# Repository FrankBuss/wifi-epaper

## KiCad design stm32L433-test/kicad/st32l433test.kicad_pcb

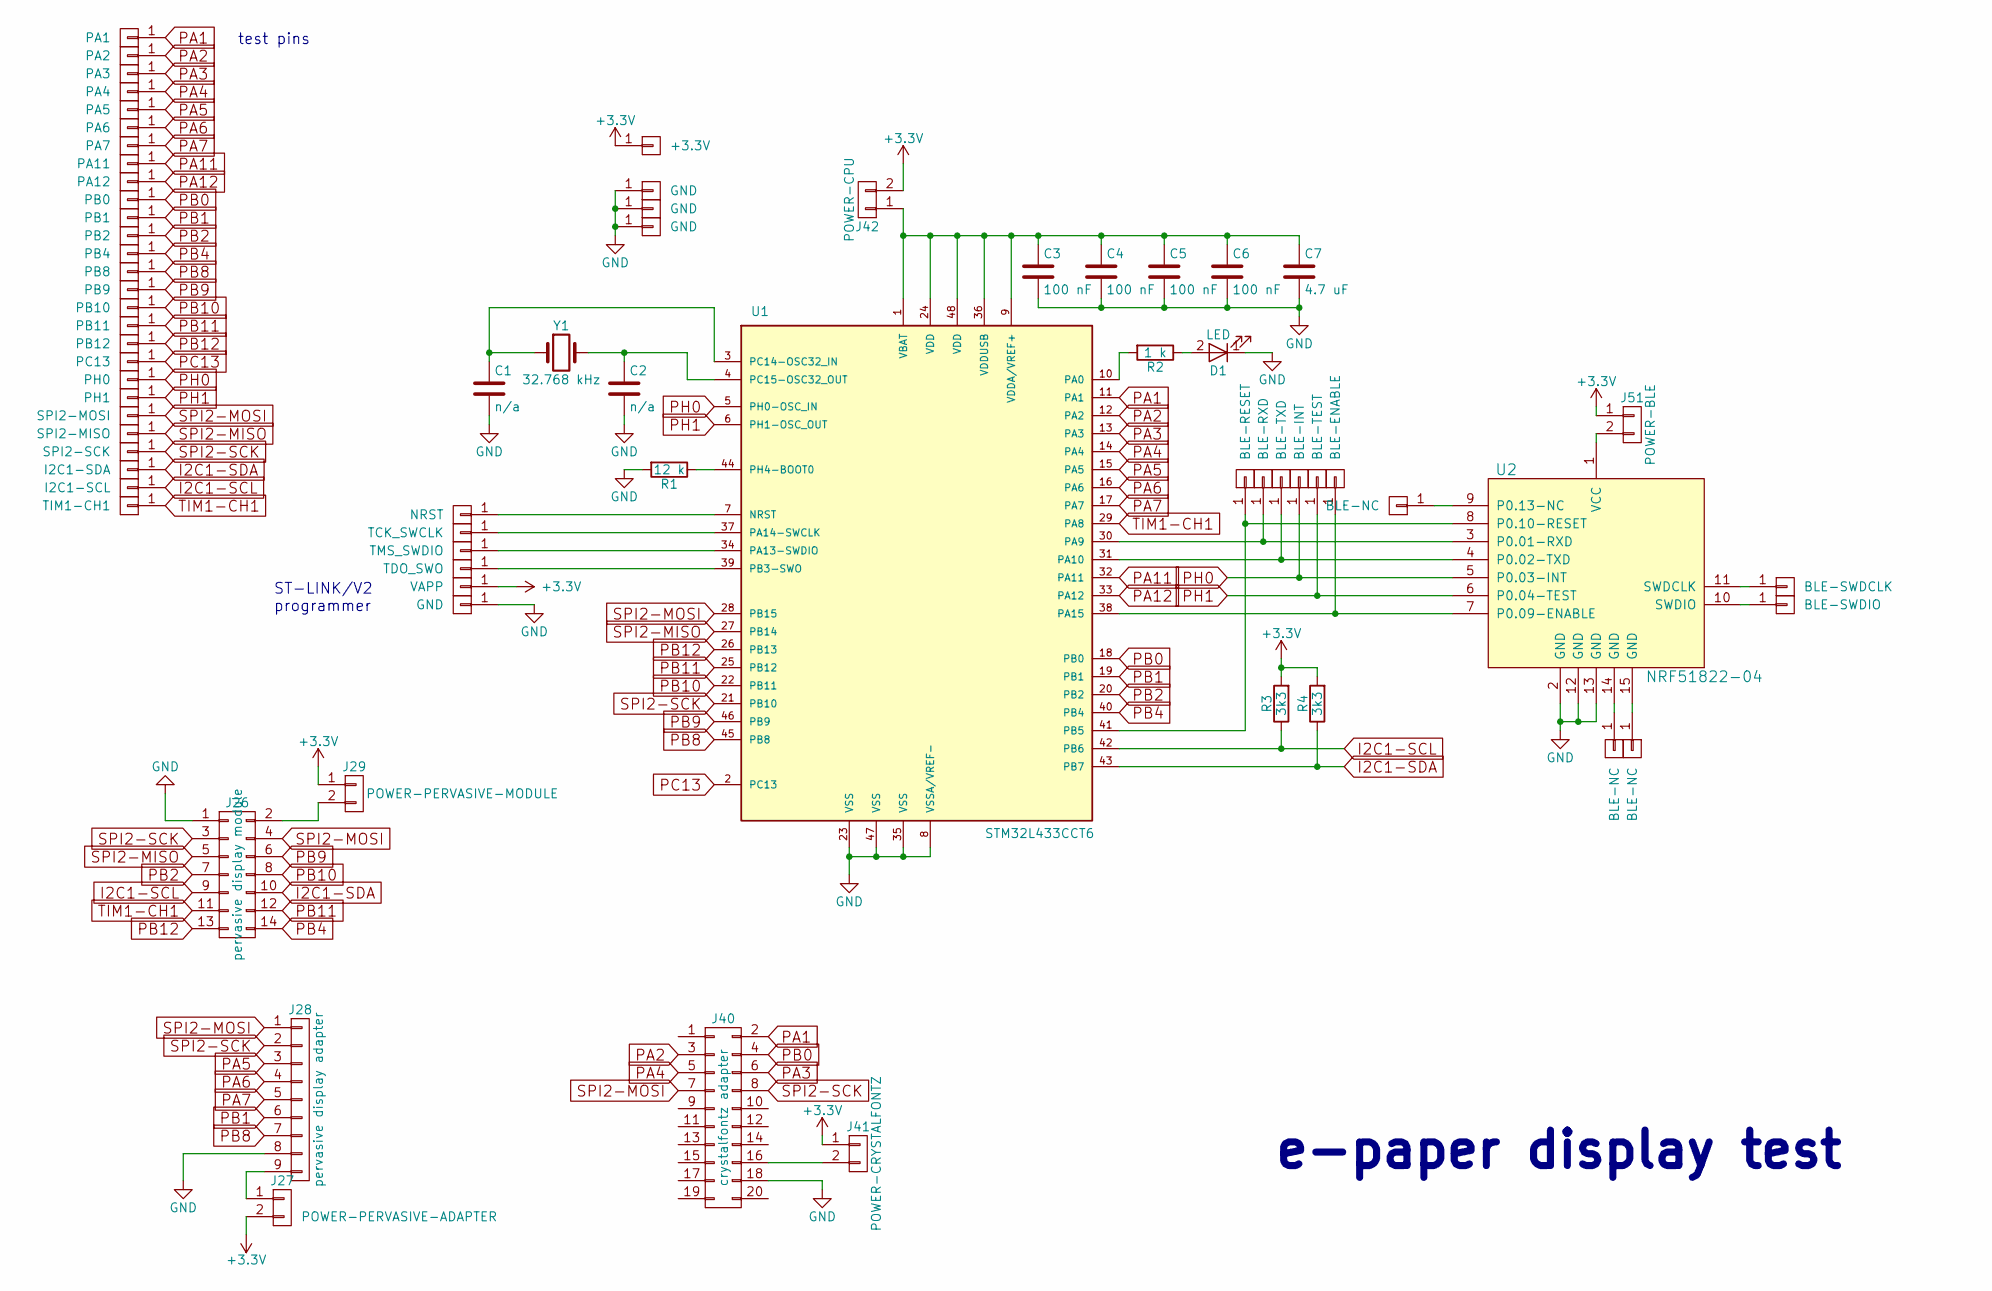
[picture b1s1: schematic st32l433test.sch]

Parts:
C1, C2: n/a; C_0805_HandSoldering
C3, C4, C5, C6: 100 nF; C_0805_HandSoldering
C7: 4.7 uF; C_0805_HandSoldering
D1: LED; LED_D3.0mm
J1: PA1; Pin_Header_Straight_1x01_Pitch2.54mm
J2: PA2; Pin_Header_Straight_1x01_Pitch2.54mm
J3: PA3; Pin_Header_Straight_1x01_Pitch2.54mm
J4: PA4; Pin_Header_Straight_1x01_Pitch2.54mm
J5: PA5; Pin_Header_Straight_1x01_Pitch2.54mm
J6: PA6; Pin_Header_Straight_1x01_Pitch2.54mm
J7: PA7; Pin_Header_Straight_1x01_Pitch2.54mm
J8: PB0; Pin_Header_Straight_1x01_Pitch2.54mm
J9: PB1; Pin_Header_Straight_1x01_Pitch2.54mm
J10: PB2; Pin_Header_Straight_1x01_Pitch2.54mm
J11: PB4; Pin_Header_Straight_1x01_Pitch2.54mm
J12: PB8; Pin_Header_Straight_1x01_Pitch2.54mm
J13: PB9; Pin_Header_Straight_1x01_Pitch2.54mm
J14: PB10; Pin_Header_Straight_1x01_Pitch2.54mm
J15: PB11; Pin_Header_Straight_1x01_Pitch2.54mm
J16: PB12; Pin_Header_Straight_1x01_Pitch2.54mm
J17: PC13; Pin_Header_Straight_1x01_Pitch2.54mm
J18: PH0; Pin_Header_Straight_1x01_Pitch2.54mm
J19: PH1; Pin_Header_Straight_1x01_Pitch2.54mm
J20: SPI2-MOSI; Pin_Header_Straight_1x01_Pitch2.54mm
J21: SPI2-MISO; Pin_Header_Straight_1x01_Pitch2.54mm
J22: SPI2-SCK; Pin_Header_Straight_1x01_Pitch2.54mm
J23: I2C1-SDA; Pin_Header_Straight_1x01_Pitch2.54mm
J24: I2C1-SCL; Pin_Header_Straight_1x01_Pitch2.54mm
J25: TIM1-CH1; Pin_Header_Straight_1x01_Pitch2.54mm
J26: pervasive display module; Pin_Header_Straight_2x07_Pitch2.54mm
J27: POWER-PERVASIVE-ADAPTER; Pin_Header_Straight_1x02_Pitch2.54mm
J28: pervasive display adapter; Pin_Header_Straight_1x09_Pitch2.54mm
J29: POWER-PERVASIVE-MODULE; Pin_Header_Straight_1x02_Pitch2.54mm
J30: NRST; Pin_Header_Straight_1x01_Pitch2.54mm
J31: TCK_SWCLK; Pin_Header_Straight_1x01_Pitch2.54mm
J32: TMS_SWDIO; Pin_Header_Straight_1x01_Pitch2.54mm
J33: TDO_SWO; Pin_Header_Straight_1x01_Pitch2.54mm
J34: VAPP; Pin_Header_Straight_1x01_Pitch2.54mm
J35, J37, J38, J39: GND; Pin_Header_Straight_1x01_Pitch2.54mm
J36: +3.3V; Pin_Header_Straight_1x01_Pitch2.54mm
J40: crystalfontz adapter; Pin_Header_Straight_2x10_Pitch2.54mm
J41: POWER-CRYSTALFONTZ; Pin_Header_Straight_1x02_Pitch2.54mm
J42: POWER-CPU; Pin_Header_Straight_1x02_Pitch2.54mm
J43: BLE-RESET; Pin_Header_Straight_1x01_Pitch2.54mm
J44: BLE-RXD; Pin_Header_Straight_1x01_Pitch2.54mm
J45: BLE-TXD; Pin_Header_Straight_1x01_Pitch2.54mm
J46: BLE-INT; Pin_Header_Straight_1x01_Pitch2.54mm
J47: BLE-TEST; Pin_Header_Straight_1x01_Pitch2.54mm
J48: BLE-ENABLE; Pin_Header_Straight_1x01_Pitch2.54mm
J49, J50, J52: BLE-NC; Pin_Header_Straight_1x01_Pitch2.54mm
J51: POWER-BLE; Pin_Header_Straight_1x02_Pitch2.54mm
J53: BLE-SWDCLK; Pin_Header_Straight_1x01_Pitch2.54mm
J54: BLE-SWDIO; Pin_Header_Straight_1x01_Pitch2.54mm
J55: PA11; Pin_Header_Straight_1x01_Pitch2.54mm
J56: PA12; Pin_Header_Straight_1x01_Pitch2.54mm
R1: 12 k; R_0805_HandSoldering
R2: 1 k; R_0805_HandSoldering
R3, R4: 3k3; R_0805_HandSoldering
U1: STM32L433CCT6; LQFP-48_7x7mm_Pitch0.5mm
U2: NRF51822-04
Y1: 32.768 kHz; crystal

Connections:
+3V3: J27.2, J29.1, J34.1, J36.1, J41.1, J42.2, J51.1, R3.2, R4.2
GND: C1.2, C2.2, C3.2, C4.2, C5.2, C6.2, C7.2, D1.1 (K), J26.1, J28.8, J35.1, J37.1, J38.1, J39.1, J40.18, R1.2, U1.8 (VSSA/VREF-), U1.23 (VSS), U1.35 (VSS), U1.47 (VSS), U2.2 (GND), U2.12 (GND), U2.13 (GND)
I2C1-SCL: J24.1, J26.9, R3.1, U1.42 (PB6)
I2C1-SDA: J23.1, J26.10, R4.1, U1.43 (PB7)
unnamed: C1.1, U1.3 (PC14-OSC32_IN), Y1.1
unnamed: C2.1, U1.4 (PC15-OSC32_OUT), Y1.2
unnamed: C3.1, C4.1, C5.1, C6.1, C7.1, J42.1, U1.1 (VBAT), U1.9 (VDDA/VREF+), U1.24 (VDD), U1.36 (VDDUSB), U1.48 (VDD)
unnamed: D1.2 (A), R2.1
unnamed: J26.2, J29.2
unnamed: J27.1, J28.9
unnamed: J30.1, U1.7 (NRST)
unnamed: J31.1, U1.37 (PA14-SWCLK)
unnamed: J32.1, U1.34 (PA13-SWDIO)
unnamed: J33.1, U1.39 (PB3-SWO)
unnamed: J40.16, J41.2
unnamed: J43.1, U1.41 (PB5), U2.8 (P0.10-RESET)
unnamed: J44.1, U1.30 (PA9), U2.3 (P0.01-RXD)
unnamed: J45.1, U1.31 (PA10), U2.4 (P0.02-TXD)
unnamed: J48.1, U1.38 (PA15), U2.7 (P0.09-ENABLE)
unnamed: J49.1, U2.9 (P0.13-NC)
unnamed: J50.1, U2.14 (GND)
unnamed: J51.2, U2.1 (VCC)
unnamed: J52.1, U2.15 (GND)
unnamed: J53.1, U2.11 (SWDCLK)
unnamed: J54.1, U2.10 (SWDIO)
unnamed: R1.1, U1.44 (PH4-BOOT0)
unnamed: R2.2, U1.10 (PA0)
PA1: J1.1, J40.2, U1.11 (PA1)
PA2: J2.1, J40.3, U1.12 (PA2)
PA3: J3.1, J40.6, U1.13 (PA3)
PA4: J4.1, J40.5, U1.14 (PA4)
PA5: J5.1, J28.3, U1.15 (PA5)
PA6: J6.1, J28.4, U1.16 (PA6)
PA7: J7.1, J28.5, U1.17 (PA7)
PA11: J55.1, U1.32 (PA11)
PA12: J56.1, U1.33 (PA12)
PB0: J8.1, J40.4, U1.18 (PB0)
PB1: J9.1, J28.6, U1.19 (PB1)
PB2: J10.1, J26.7, U1.20 (PB2)
PB4: J11.1, J26.14, U1.40 (PB4)
PB8: J12.1, J28.7, U1.45 (PB8)
PB9: J13.1, J26.6, U1.46 (PB9)
PB10: J14.1, J26.8, U1.22 (PB11)
PB11: J15.1, J26.12, U1.25 (PB12)
PB12: J16.1, J26.13, U1.26 (PB13)
PC13: J17.1, U1.2 (PC13)
PH0: J18.1, J46.1, U1.5 (PH0-OSC_IN), U2.5 (P0.03-INT)
PH1: J19.1, J47.1, U1.6 (PH1-OSC_OUT), U2.6 (P0.04-TEST)
SPI2-MISO: J21.1, J26.5, U1.27 (PB14)
SPI2-MOSI: J20.1, J26.4, J28.1, J40.7, U1.28 (PB15)
SPI2-SCK: J22.1, J26.3, J28.2, J40.8, U1.21 (PB10)
TIM1-CH1: J25.1, J26.11, U1.29 (PA8)

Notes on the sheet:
ST-LINK/V2 programmer
test pins
e-paper display test

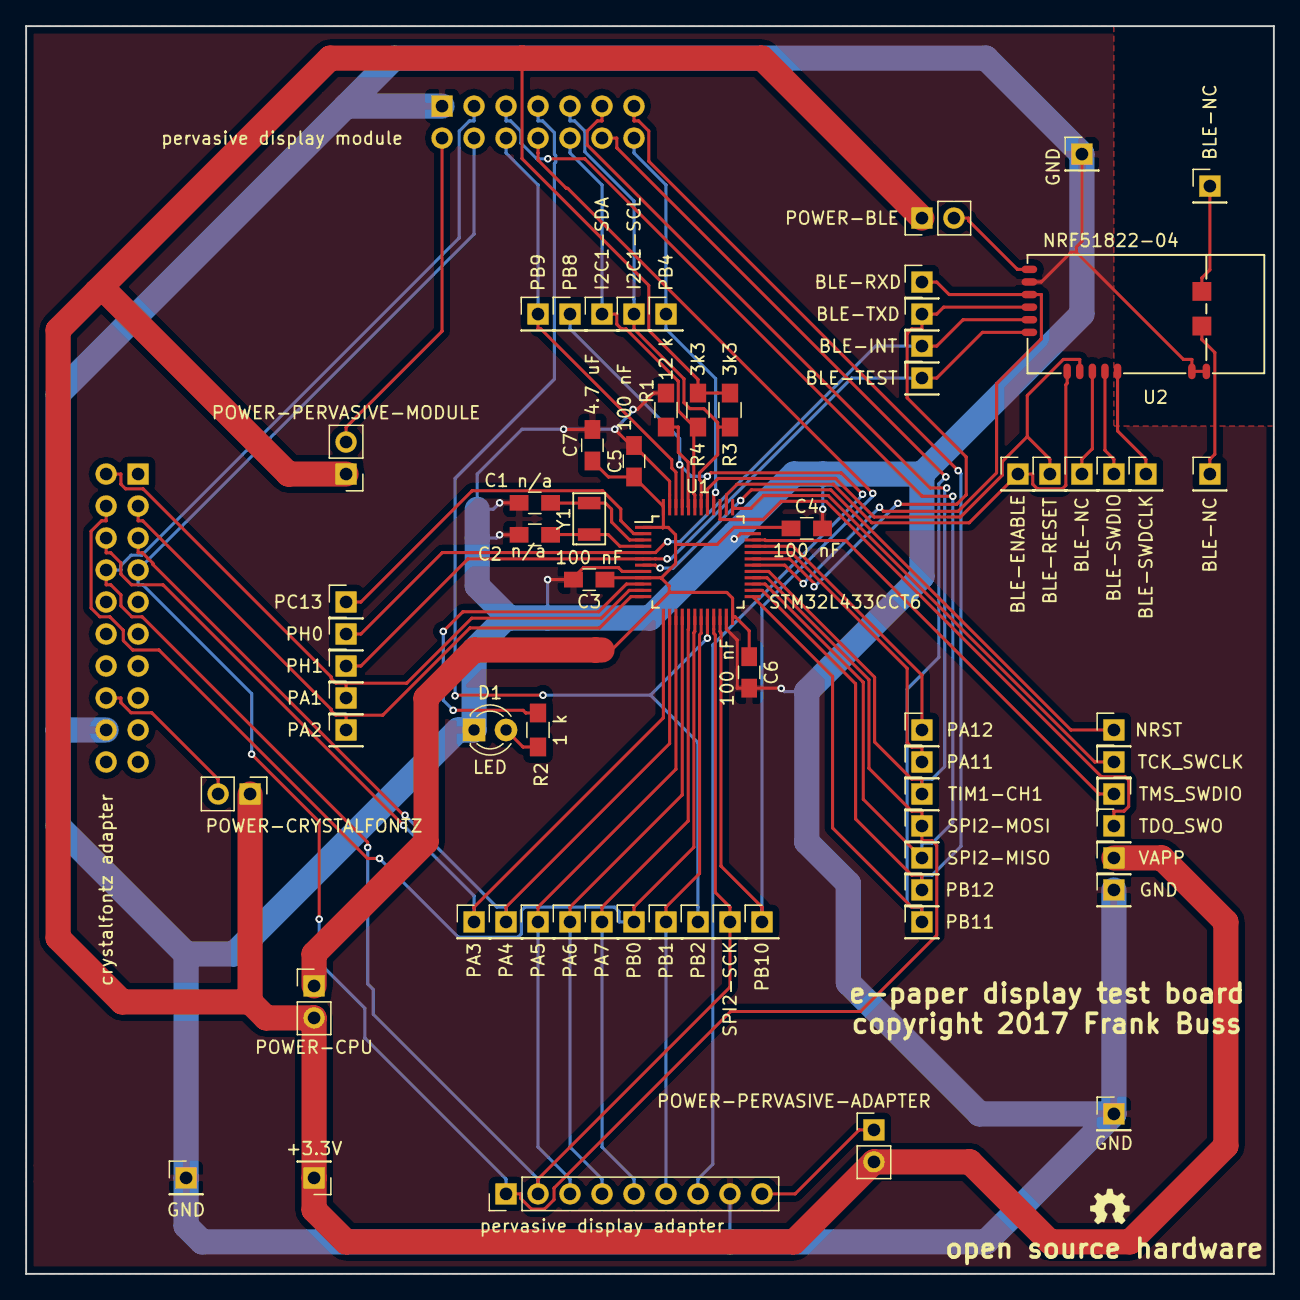
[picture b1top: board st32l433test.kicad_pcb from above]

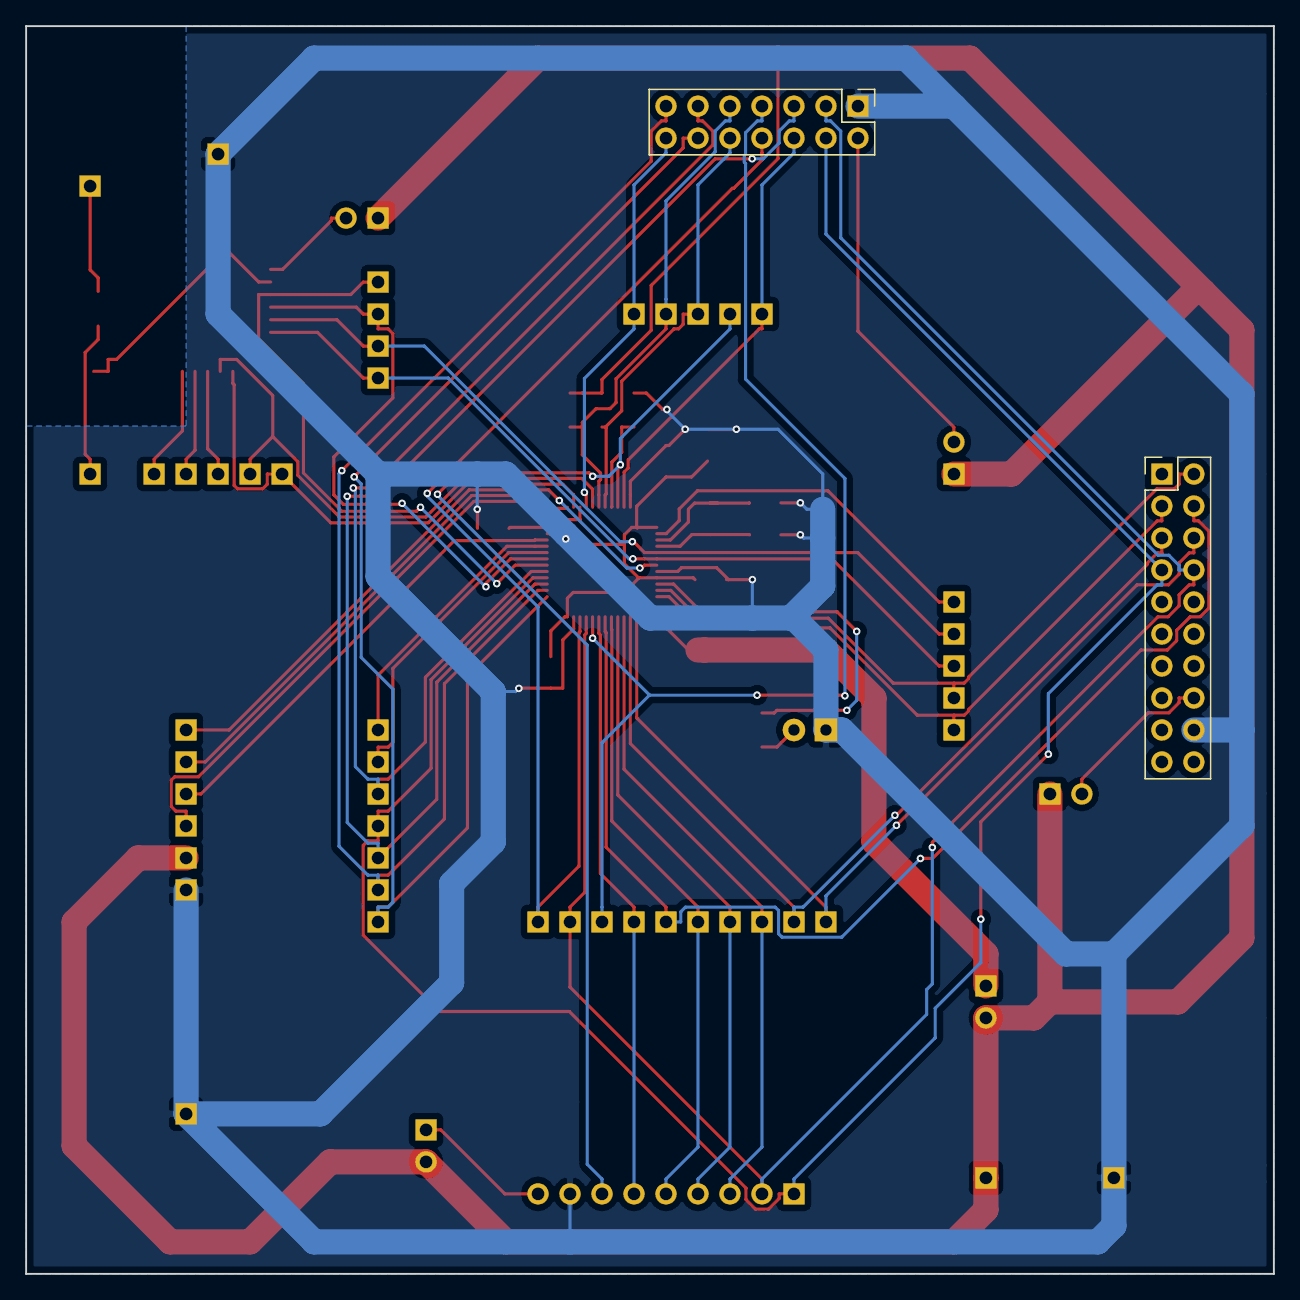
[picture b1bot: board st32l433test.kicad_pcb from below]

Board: 2 copper layers, 99.1 x 99.1 mm, 71 parts (2 on the bottom side), 52 nets.

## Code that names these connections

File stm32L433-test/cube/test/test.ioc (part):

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Mcu.Name=STM32L433C(B-C)Tx
Mcu.Package=LQFP48
Mcu.UserName=STM32L433CCTx
PA0.Signal=GPIO_Output
PA1.Signal=GPIO_Output
PA10.Mode=Asynchronous
PA10.Signal=USART1_RX
PA11.Mode=Device
PA11.Signal=USB_DM
PA12.Mode=Device
PA12.Signal=USB_DP
PA13\ (JTMS-SWDIO).Mode=Serial_Wire
PA13\ (JTMS-SWDIO).Signal=SYS_JTMS-SWDIO
PA14\ (JTCK-SWCLK).Mode=Serial_Wire
PA14\ (JTCK-SWCLK).Signal=SYS_JTCK-SWCLK
PA2.Signal=GPIO_Output
PA3.Signal=GPIO_Output
PA4.Signal=GPIO_Output
PA5.Signal=GPIO_Output
PA6.Signal=GPIO_Output
PA7.Signal=GPIO_Output
PA8.Signal=S_TIM1_CH1
PA9.Mode=Asynchronous
PA9.Signal=USART1_TX
PB0.Signal=GPIO_Input
PB1.Signal=GPIO_Input
PB10.Mode=Full_Duplex_Master
PB10.Signal=SPI2_SCK
PB14.Mode=Full_Duplex_Master
PB14.Signal=SPI2_MISO
PB15.Mode=Full_Duplex_Master
PB15.Signal=SPI2_MOSI
PB2.Signal=GPIO_Input
PB3\ (JTDO-TRACESWO).Signal=SYS_JTDO-SWO
PB4\ (NJTRST).Signal=GPIO_Output
PB6.Mode=I2C
PB6.Signal=I2C1_SCL
PB7.Mode=I2C
PB7.Signal=I2C1_SDA
PC14-OSC32_IN\ (PC14).Mode=LSE-External-Oscillator
PC14-OSC32_IN\ (PC14).Signal=RCC_OSC32_IN
PC15-OSC32_OUT\ (PC15).Mode=LSE-External-Oscillator
PC15-OSC32_OUT\ (PC15).Signal=RCC_OSC32_OUT
RCC.HSE_VALUE=8000000
RCC.SYSCLKFreq_VALUE=48000000
board=test

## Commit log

2017-04-14 first working prototype
2017-04-29 solar cell test and new datasheets
2017-05-06 testing the new 4.2" black/white/red ePaper display
2017-05-07 better contrast
2017-06-18 STM32L433 e-paper display test project

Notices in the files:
stm32L433-test/kicad/st32l433test.kicad_pcb:
copyright 2017 Frank Buss
